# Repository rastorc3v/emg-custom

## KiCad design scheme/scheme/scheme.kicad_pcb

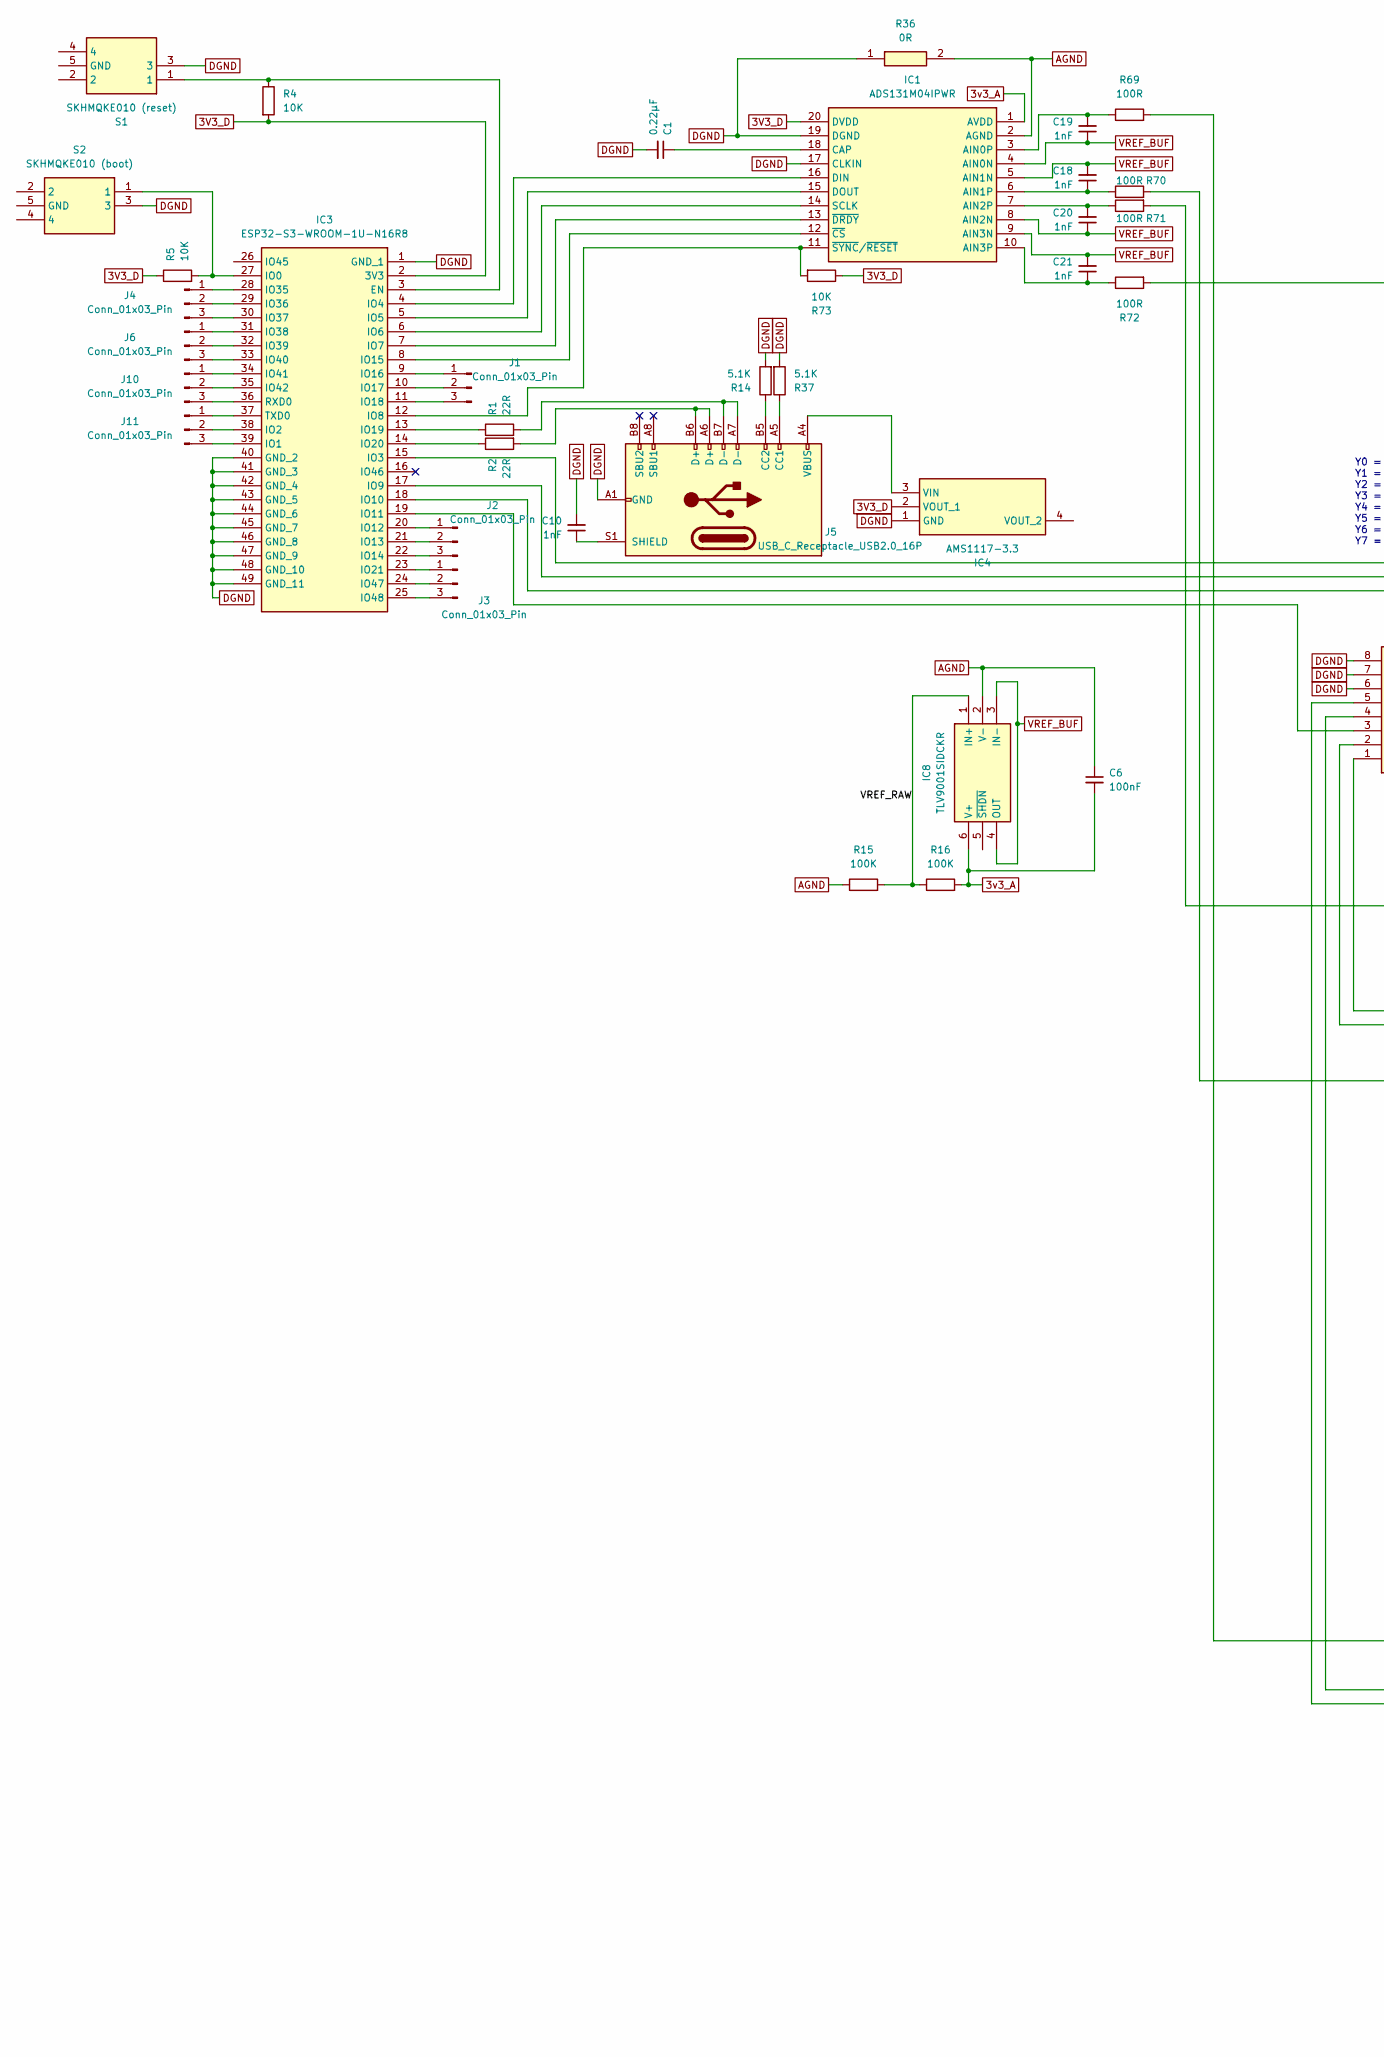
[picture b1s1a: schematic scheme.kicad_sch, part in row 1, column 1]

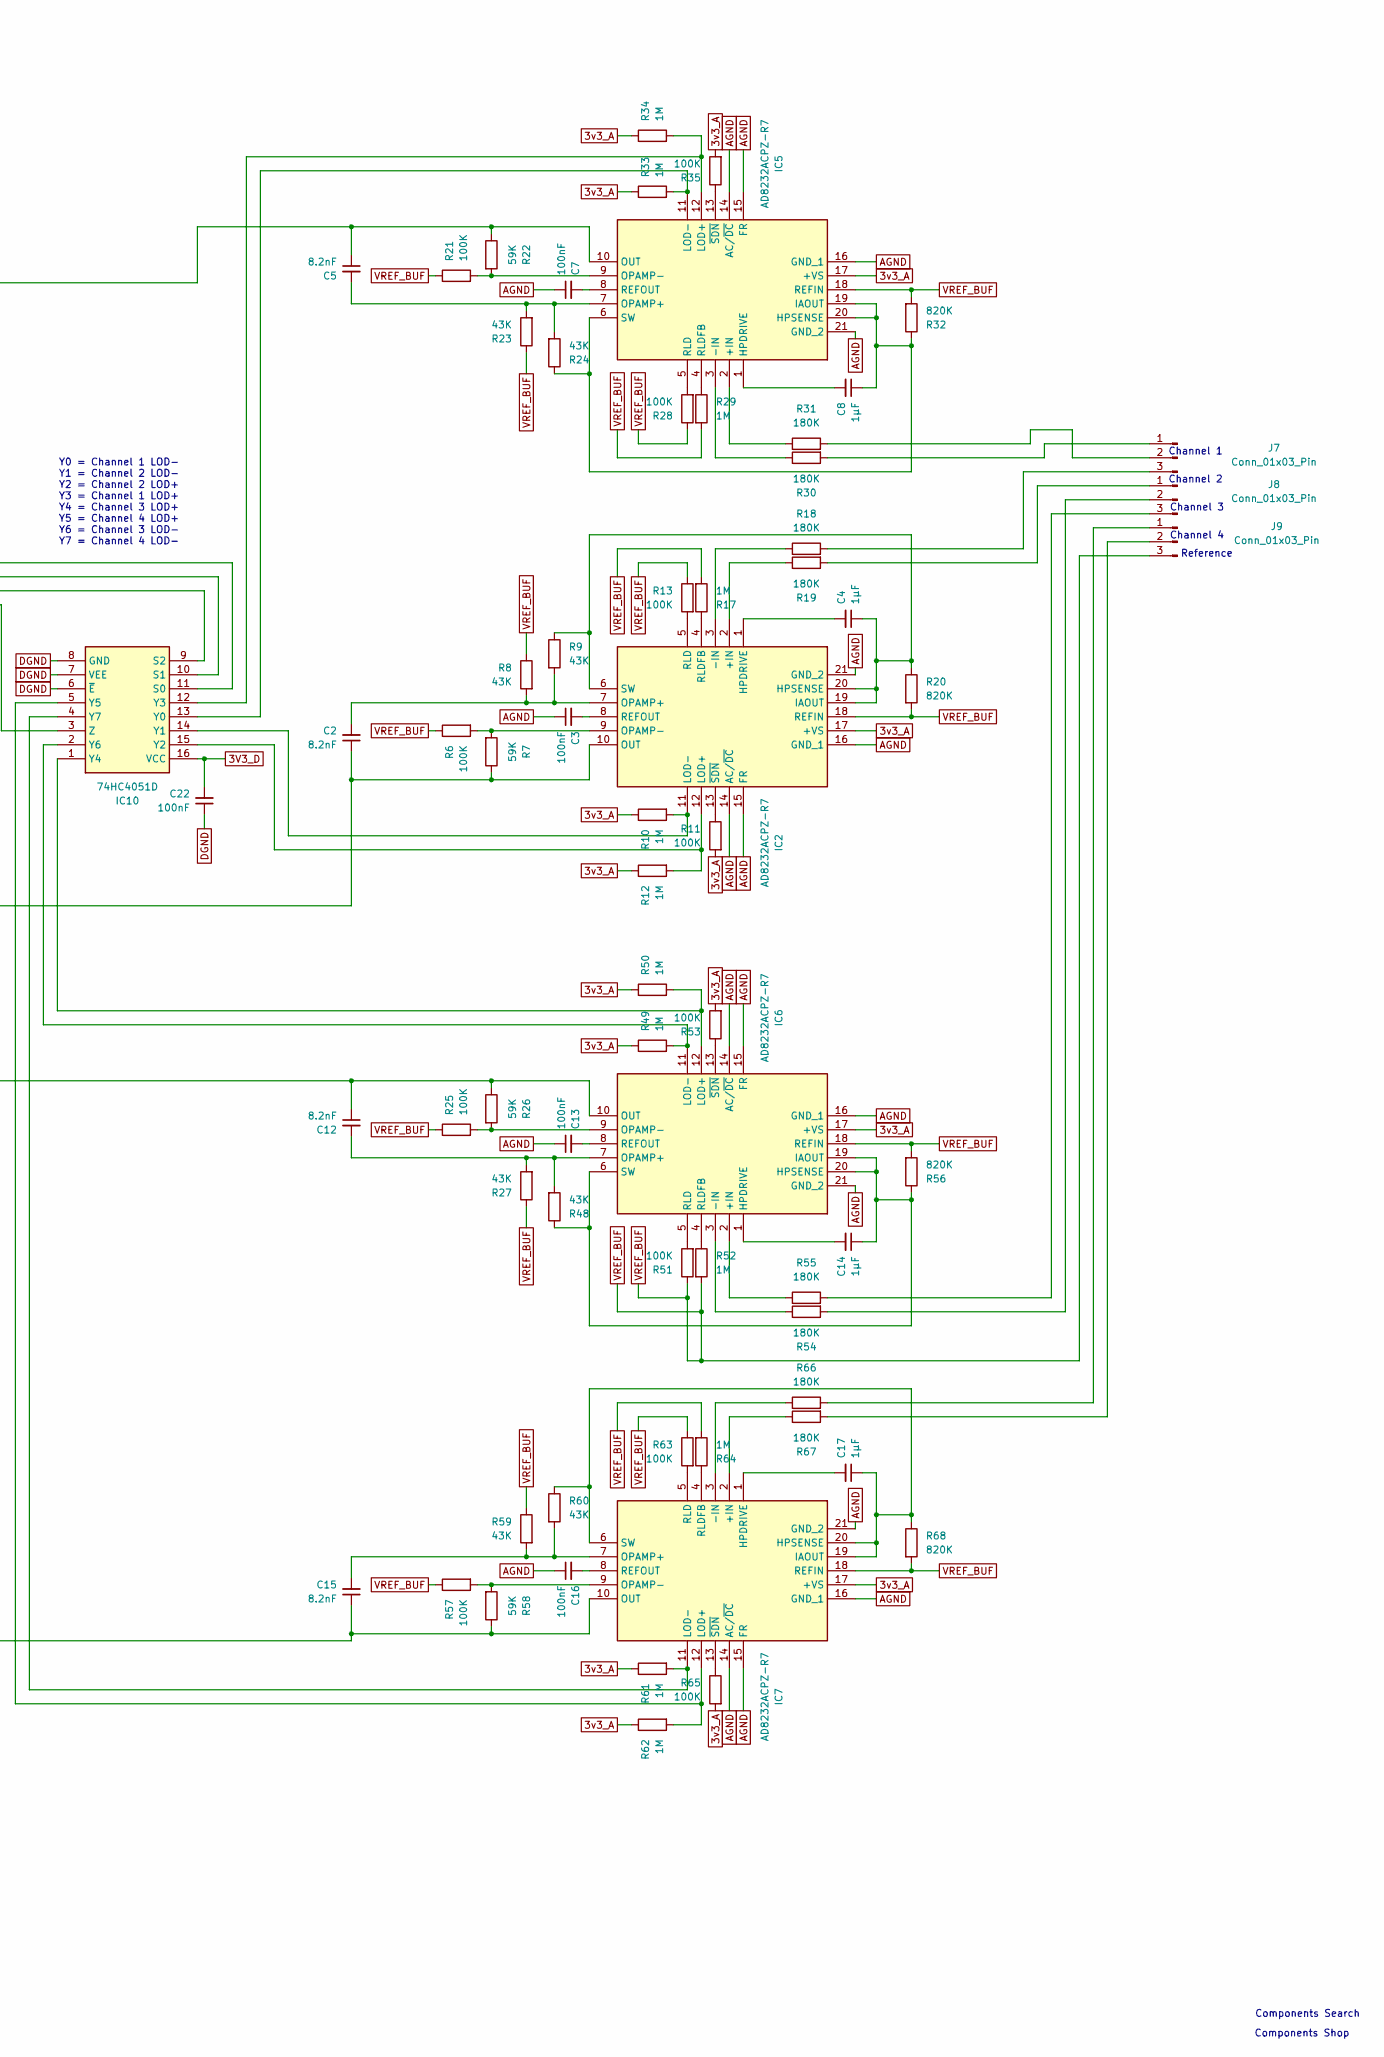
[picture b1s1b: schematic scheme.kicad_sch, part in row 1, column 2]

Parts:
C1: 0.22µF; C_0805_2012Metric
C2, C5, C12, C15: 8.2nF; C_0805_2012Metric
C3, C6, C7, C13, C16, C22: 100nF; C_0805_2012Metric
C4, C8, C14, C17: 1µF; C_0805_2012Metric
C10, C18, C19, C20, C21: 1nF; C_0805_2012Metric
IC1: ADS131M04IPWR; SOP65P640X120-20N; Manufacturer_Part_Number ADS131M04IPWR; Mouser Part Number 595-ADS131M04IPWR
IC2, IC5, IC6, IC7: AD8232ACPZ-R7; QFN50P400X400X80-21N-D; Manufacturer_Part_Number AD8232ACPZ-R7; Mouser Part Number 584-AD8232ACPZ-R7
IC3: ESP32-S3-WROOM-1U-N16R8; ESP32S3WROOM1UN16R8; Manufacturer_Part_Number ESP32-S3-WROOM-1U-N16R8; Mouser Part Number 356-ESP32S3WM1UN16R8
IC4: AMS1117-3.3; SOT229P700X180-4N; Manufacturer_Part_Number AMS1117-3.3
IC8: TLV9001SIDCKR; SOT65P210X110-6N; Manufacturer_Part_Number TLV9001SIDCKR; Mouser Part Number 595-TLV9001SIDCKR
IC10: 74HC4051D; SOIC127P600X175-16N; Manufacturer_Part_Number 74HC4051D; Mouser Part Number N/A
J1, J2, J3, J4, J6, J10, J11: Conn_01x03_Pin; PinHeader_1x03_P1.00mm_Vertical
J5: USB_C_Receptacle_USB2.0_16P; USB_C_Receptacle_HCTL_HC-TYPE-C-16P-01A
J7, J8, J9: Conn_01x03_Pin; PinHeader_1x03_P1.00mm_Horizontal
R1, R2: 22R; R_0805_2012Metric
R4, R5, R73: 10K; R_0805_2012Metric
R6, R11, R13, R15, R16, R21, R25, R28, R35, R51, R53, R57, R63, R65: 100K; R_0805_2012Metric
R7, R22, R26, R58: 59K; R_0805_2012Metric
R8, R9, R23, R24, R27, R48, R59, R60: 43K; R_0805_2012Metric
R10, R12, R17, R29, R33, R34, R49, R50, R52, R61, R62, R64: 1M; R_0805_2012Metric
R14, R37: 5.1K; RESC2012X60N
R18, R19, R30, R31, R54, R55, R66, R67: 180K; R_0805_2012Metric
R20, R32, R56, R68: 820K; R_0805_2012Metric
R36: 0R; R_0805_2012Metric; Manufacturer_Part_Number CRCW12060000Z0EA; Mouser Part Number 71-CRCW1206-0-E3
R69, R70, R71, R72: 100R; R_0805_2012Metric
S1: SKHMQKE010 (reset); SKHMQLE010; Manufacturer_Part_Number SKHMQKE010; Mouser Part Number 688-SKHMQKE010
S2: SKHMQKE010 (boot); SKHMQLE010; Manufacturer_Part_Number SKHMQKE010; Mouser Part Number 688-SKHMQKE010

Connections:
3V3_D: C22.2, IC1.20 (DVDD), IC3.2 (3V3), IC4.2 (VOUT_1), IC10.16 (VCC), R4.2, R5.1, R73.1
3v3_A: C6.2, IC1.1 (AVDD), IC2.17 (+VS), IC5.17 (+VS), IC6.17 (+VS), IC7.17 (+VS), IC8.6 (V+), R10.1, R11.2, R12.1, R16.2, R33.1, R34.1, R35.2, R49.1, R50.1, R53.2, R61.1, R62.1, R65.2
/VREF_RAW: IC8.1 (IN+), R15.2, R16.1
AGND: C3.1, C6.1, C7.1, C13.1, C16.1, IC1.2 (AGND), IC2.14 (AC/~DC), IC2.15 (FR), IC2.16 (GND_1), IC2.21 (GND_2), IC5.14 (AC/~DC), IC5.15 (FR), IC5.16 (GND_1), IC5.21 (GND_2), IC6.14 (AC/~DC), IC6.15 (FR), IC6.16 (GND_1), IC6.21 (GND_2), IC7.14 (AC/~DC), IC7.15 (FR), IC7.16 (GND_1), IC7.21 (GND_2), IC8.2 (V-), R15.1, R36.2
DGND: C1.2, C10.2, C22.1, IC1.17 (CLKIN), IC1.19 (DGND), IC3.1 (GND_1), IC3.40 (GND_2), IC3.41 (GND_3), IC3.42 (GND_4), IC3.43 (GND_5), IC3.44 (GND_6), IC3.45 (GND_7), IC3.46 (GND_8), IC3.47 (GND_9), IC3.48 (GND_10), IC3.49 (GND_11), IC4.1 (GND), IC10.6 (~E), IC10.7 (VEE), IC10.8 (GND), J5.A1 (GND), J5.A12 (GND), J5.B1 (GND), J5.B12 (GND), R14.2, R36.1, R37.2, S1.3, S2.3
unnamed: C19.2, IC1.3 (AIN0P), R69.1
unnamed: C18.1, IC1.6 (AIN1P), R70.1
unnamed: C20.2, IC1.7 (AIN2P), R71.1
unnamed: C21.1, IC1.10 (AIN3P), R72.1
unnamed: C1.1, IC1.18 (CAP)
unnamed: IC1.16 (DIN), IC3.4 (IO4)
unnamed: IC1.15 (DOUT), IC3.5 (IO5)
unnamed: IC1.14 (SCLK), IC3.6 (IO6)
unnamed: IC1.12 (~CS), IC3.8 (IO15)
unnamed: IC1.13 (~DRDY), IC3.7 (IO7)
unnamed: IC1.11 (~SYNC/~RESET), IC3.12 (IO8), R73.2
unnamed: IC2.2 (+IN), R19.1
unnamed: IC2.3 (-IN), R18.1
unnamed: C4.2, IC2.1 (HPDRIVE)
unnamed: C4.1, IC2.6 (SW), IC2.19 (IAOUT), IC2.20 (HPSENSE), R9.1, R20.1
unnamed: C2.2, IC2.7 (OPAMP+), R8.2, R9.2
unnamed: IC2.9 (OPAMP-), R6.2, R7.2
unnamed: C2.1, IC2.10 (OUT), R7.1, R71.2
unnamed: C3.2, IC2.8 (REFOUT)
unnamed: IC2.5 (RLD), R13.2
unnamed: IC2.4 (RLDFB), R17.1
unnamed: IC2.13 (~SDN), R11.1
unnamed: IC3.3 (EN), R4.1, S1.1
unnamed: IC3.27 (IO0), R5.2, S2.1
unnamed: IC3.39 (IO1), J11.3
unnamed: IC3.38 (IO2), J11.2
unnamed: IC3.20 (IO12), J2.1
unnamed: IC3.21 (IO13), J2.2
unnamed: IC3.22 (IO14), J2.3
unnamed: IC3.9 (IO16), J1.1
unnamed: IC3.10 (IO17), J1.2
unnamed: IC3.11 (IO18), J1.3
unnamed: IC3.13 (IO19), R1.1
unnamed: IC3.14 (IO20), R2.1
unnamed: IC3.23 (IO21), J3.1
unnamed: IC3.28 (IO35), J4.1
unnamed: IC3.29 (IO36), J4.2
unnamed: IC3.30 (IO37), J4.3
unnamed: IC3.31 (IO38), J6.1
unnamed: IC3.32 (IO39), J6.2
unnamed: IC3.33 (IO40), J6.3
unnamed: IC3.34 (IO41), J10.1
unnamed: IC3.35 (IO42), J10.2
unnamed: IC3.24 (IO47), J3.2
unnamed: IC3.25 (IO48), J3.3
unnamed: IC3.36 (RXD0), J10.3
unnamed: IC3.37 (TXD0), J11.1
unnamed: IC4.3 (VIN), J5.A4 (VBUS), J5.A9 (VBUS), J5.B4 (VBUS), J5.B9 (VBUS)
unnamed: IC5.2 (+IN), R31.1
unnamed: IC5.3 (-IN), R30.1
unnamed: C8.2, IC5.1 (HPDRIVE)
unnamed: C8.1, IC5.6 (SW), IC5.19 (IAOUT), IC5.20 (HPSENSE), R24.1, R32.1
unnamed: C5.2, IC5.7 (OPAMP+), R23.2, R24.2
unnamed: IC5.9 (OPAMP-), R21.2, R22.2
unnamed: C5.1, IC5.10 (OUT), R22.1, R72.2
unnamed: C7.2, IC5.8 (REFOUT)
unnamed: IC5.5 (RLD), R28.2
unnamed: IC5.4 (RLDFB), R29.1
unnamed: IC5.13 (~SDN), R35.1
unnamed: IC6.2 (+IN), R55.1
unnamed: IC6.3 (-IN), R54.1
unnamed: C14.2, IC6.1 (HPDRIVE)
unnamed: C14.1, IC6.6 (SW), IC6.19 (IAOUT), IC6.20 (HPSENSE), R48.1, R56.1
unnamed: C12.2, IC6.7 (OPAMP+), R27.2, R48.2
unnamed: IC6.9 (OPAMP-), R25.2, R26.2
unnamed: C12.1, IC6.10 (OUT), R26.1, R70.2
unnamed: C13.2, IC6.8 (REFOUT)
unnamed: IC6.5 (RLD), R51.2
unnamed: IC6.4 (RLDFB), R52.1
unnamed: IC6.13 (~SDN), R53.1
unnamed: IC7.2 (+IN), R67.1
unnamed: IC7.3 (-IN), R66.1
unnamed: C17.2, IC7.1 (HPDRIVE)
unnamed: C17.1, IC7.6 (SW), IC7.19 (IAOUT), IC7.20 (HPSENSE), R60.1, R68.1
unnamed: C15.2, IC7.7 (OPAMP+), R59.2, R60.2
unnamed: IC7.9 (OPAMP-), R57.2, R58.2
unnamed: C15.1, IC7.10 (OUT), R58.1, R69.2
unnamed: C16.2, IC7.8 (REFOUT)
unnamed: IC7.5 (RLD), R63.2
unnamed: IC7.4 (RLDFB), R64.1
unnamed: IC7.13 (~SDN), R65.1
unnamed: IC3.15 (IO3), IC10.11 (S0)
unnamed: IC3.17 (IO9), IC10.10 (S1)
unnamed: IC3.18 (IO10), IC10.9 (S2)
unnamed: IC5.11 (LOD-), IC10.13 (Y0), R33.2
unnamed: IC2.11 (LOD-), IC10.14 (Y1), R10.2
unnamed: IC2.12 (LOD+), IC10.15 (Y2), R12.2
unnamed: IC5.12 (LOD+), IC10.12 (Y3), R34.2
unnamed: IC6.12 (LOD+), IC10.1 (Y4), R50.2
unnamed: IC7.12 (LOD+), IC10.5 (Y5), R62.2
unnamed: IC6.11 (LOD-), IC10.2 (Y6), R49.2
unnamed: IC7.11 (LOD-), IC10.4 (Y7), R61.2
unnamed: IC3.19 (IO11), IC10.3 (Z)
unnamed: J5.A5 (CC1), R37.1
unnamed: J5.B5 (CC2), R14.1
unnamed: J5.A6 (D+), J5.B6 (D+), R2.2
unnamed: J5.A7 (D-), J5.B7 (D-), R1.2
unnamed: C10.1, J5.S1 (SHIELD)
unnamed: J7.1, R30.2
unnamed: J7.2, R31.2
unnamed: J7.3, R18.2
unnamed: J8.1, R19.2
unnamed: J8.2, R54.2
unnamed: J8.3, R55.2
unnamed: J9.1, R66.2
unnamed: J9.2, R67.2
VREF_BUF: C18.2, C19.1, C20.1, C21.2, IC1.4 (AIN0N), IC1.5 (AIN1N), IC1.8 (AIN2N), IC1.9 (AIN3N), IC2.18 (REFIN), IC5.18 (REFIN), IC6.18 (REFIN), IC7.18 (REFIN), IC8.3 (IN-), IC8.4 (OUT), J9.3, R6.1, R8.1, R13.1, R17.2, R20.2, R21.1, R23.1, R25.1, R27.1, R28.1, R29.2, R32.2, R51.1, R52.2, R56.2, R57.1, R59.1, R63.1, R64.2, R68.2

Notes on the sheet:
Y0 = Channel 1 LOD- Y1 = Channel 2 LOD- Y2 = Channel 2 LOD+ Y3 = Channel 1 LOD+ Y4 = Channel 3 LOD+ Y5 = Channel 4 LOD+ Y6 = Channel 3 LOD- Y7 = Channel 4 LOD-
Channel 1
Reference
Components Search
Channel 4
Channel 2
Channel 3
Components Shop

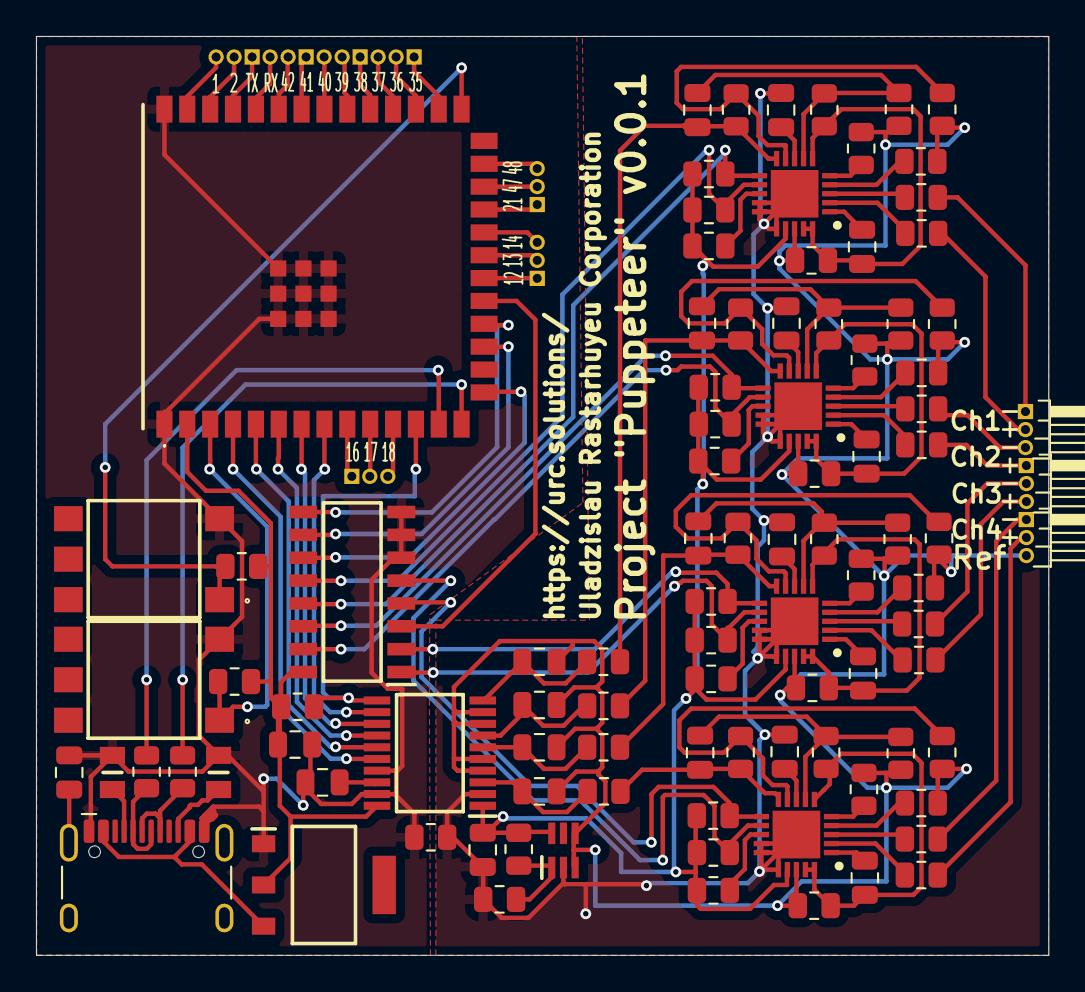
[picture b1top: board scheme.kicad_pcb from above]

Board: 2 copper layers, 56.2 x 51.0 mm, 104 parts (0 on the bottom side), 112 nets.

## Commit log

2025-12-21 Initial commit with README
2025-12-28 complete first version: scheme + pcb
2025-12-28 first release 0.0.1
